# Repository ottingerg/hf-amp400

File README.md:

# hf-amp400

HF-Amp400 is controllerboard designed to controll the gate biasing and output power of 2 double HF-AMP FETs. 

It therefore provides 4 channels of gate biasing

4 channels of HF-Power mesaurement 

2 resetable fuses up to 10A and one auxilary resetable fuse controll for even higher currents.

This project was done as collaberation between

EMV-Consulting (http://www.emvconsulting.at)

Otelo eGen (http://www.oteloegen.at)

and

Karl Zeilhofer (http://www.zeilhofer.co.at)

it is Open Source Hardware licensed under CC-BY-SA 3.0 and is based on EtherDue which itself is based on Arduino Due

# EtherDue

The EtherDue is an 100% Arduino Due compatible board with onboard Ethernet.

For full details about the EtherDue, including a getting started guide, please visit the [Freetronics EtherDue product page](http://www.freetronics.com/products/etherdue-arduino-due-compatible-with-onboard-ethernet).

Design files were produced with [Kicad](http://kicad.org). A [PDF of the schematic is available](https://github.com/freetronics/EtherDue/raw/master/EtherDue.pdf).

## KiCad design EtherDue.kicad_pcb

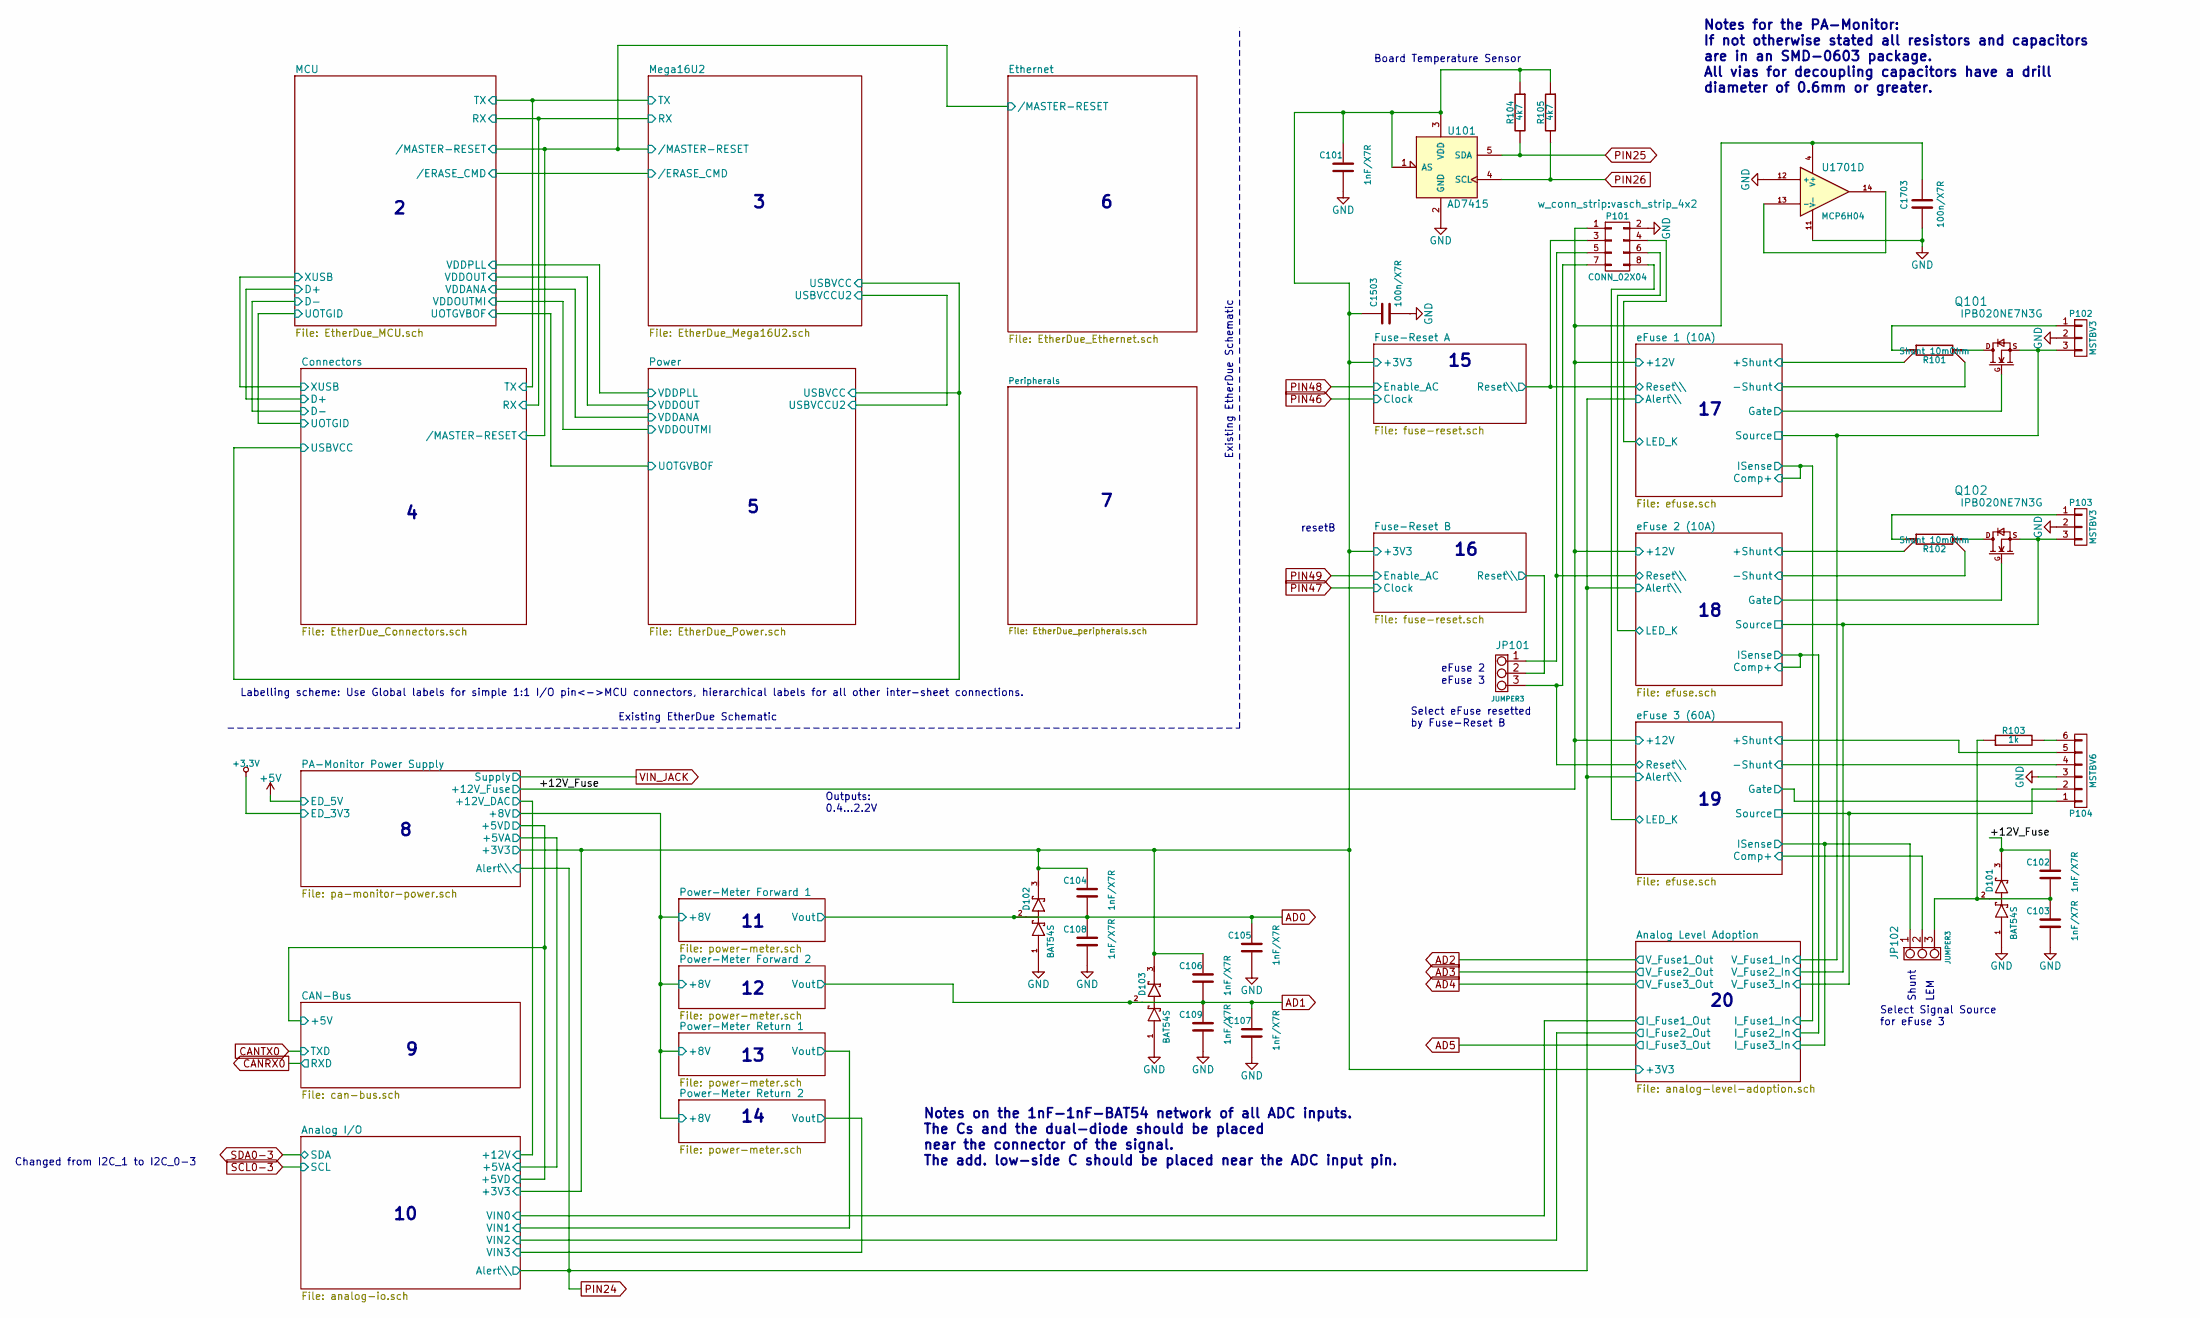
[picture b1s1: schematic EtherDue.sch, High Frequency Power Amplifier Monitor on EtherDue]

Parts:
C101, C102, C103, C104, C105, C106, C107, C108, C109: 1nF/X7R; C_0603
C1503, C1703: 100n/X7R; C_0603
D101, D102, D103: BAT54S; sot23
JP101, JP102: JUMPER3; Pin_Header_Straight_1x03
P101: CONN_02X04; vasch_strip_4x2
P102, P103: MSTBV3
P104: MSTBV6
Q101, Q102: IPB020NE7N3G; d2-pak
R101, R102: Shunt 10mOhm; WSL4026
R103: 1k; R_0603
R104, R105: 4k7; R_0603
U101: AD7415; SOT23-5
U1701: MCP6H04; SOIC-14_3.9x8.7mm_Pitch1.27mm

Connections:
/Analog I/O/+3V3: C101.1, C104.1, C106.1, C1503.1, D102.3 (cathode), D103.3 (cathode), R104.1, R105.1, U101.1 (AS), U101.3 (VDD); also elsewhere on the board
/Fuse-Reset B/Reset\: JP101.2; also elsewhere on the board
/eFuse 1 (10A)/+Shunt: R101.SA; also elsewhere on the board
/eFuse 1 (10A)/-Shunt: R101.SB; also elsewhere on the board
/eFuse 1 (10A)/Gate: Q101.G; also elsewhere on the board
/eFuse 1 (10A)/LED_K: P101.4; also elsewhere on the board
/eFuse 1 (10A)/Source: P102.3, Q101.S; also elsewhere on the board
/eFuse 2 (10A)/+Shunt: R102.SA; also elsewhere on the board
/eFuse 2 (10A)/-Shunt: R102.SB; also elsewhere on the board
/eFuse 2 (10A)/Gate: Q102.G; also elsewhere on the board
/eFuse 2 (10A)/LED_K: P101.6; also elsewhere on the board
/eFuse 2 (10A)/Reset\: JP101.1, P101.5; also elsewhere on the board
/eFuse 2 (10A)/Source: P103.3, Q102.S; also elsewhere on the board
/eFuse 3 (60A)/+Shunt: P104.5; also elsewhere on the board
/eFuse 3 (60A)/-Shunt: P104.4; also elsewhere on the board
/eFuse 3 (60A)/Comp+: JP102.2; also elsewhere on the board
/eFuse 3 (60A)/Gate: P104.1; also elsewhere on the board
/eFuse 3 (60A)/ISense: JP102.1; also elsewhere on the board
/eFuse 3 (60A)/LED_K: P101.8; also elsewhere on the board
/eFuse 3 (60A)/Reset\: JP101.3, P101.7; also elsewhere on the board
/eFuse 3 (60A)/Source: P104.2; also elsewhere on the board
AD0: C104.2, C105.1, C108.1, D102.2 (AK); also elsewhere on the board
AD1: C106.2, C107.1, C109.1, D103.2 (AK); also elsewhere on the board
unnamed: C102.2, C103.1, D101.2 (AK), JP102.3, R103.1
unnamed: P102.1, R101.A
unnamed: P103.1, R102.A
unnamed: P104.6, R103.2
unnamed: Q101.D, R101.B
unnamed: Q102.D, R102.B
unnamed: U1701.13 (-), U1701.14
PIN25: R104.2, U101.5 (SDA); also elsewhere on the board
PIN26: R105.2, U101.4 (SCL); also elsewhere on the board

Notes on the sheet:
Labelling scheme: Use Global labels for simple 1:1 I/O pin<->MCU connectors, hierarchical labels for all other inter-sheet connections.
Existing EtherDue Schematic
Outputs: 0.4...2.2V
resetB
Board Temperature Sensor
Notes for the PA-Monitor: If not otherwise stated all resistors and capacitors are in an SMD-0603 package. All vias for decoupling capacitors have a drill diameter of 0.6mm or greater.
Notes on the 1nF-1nF-BAT54 network of all ADC inputs. The Cs and the dual-diode should be placed near the connector of the signal. The add. low-side C should be placed near the ADC input pin.
Shunt
LEM
Select Signal Source for eFuse 3
Select eFuse resetted by Fuse-Reset B
eFuse 2
eFuse 3
Changed from I2C_1 to I2C_0-3

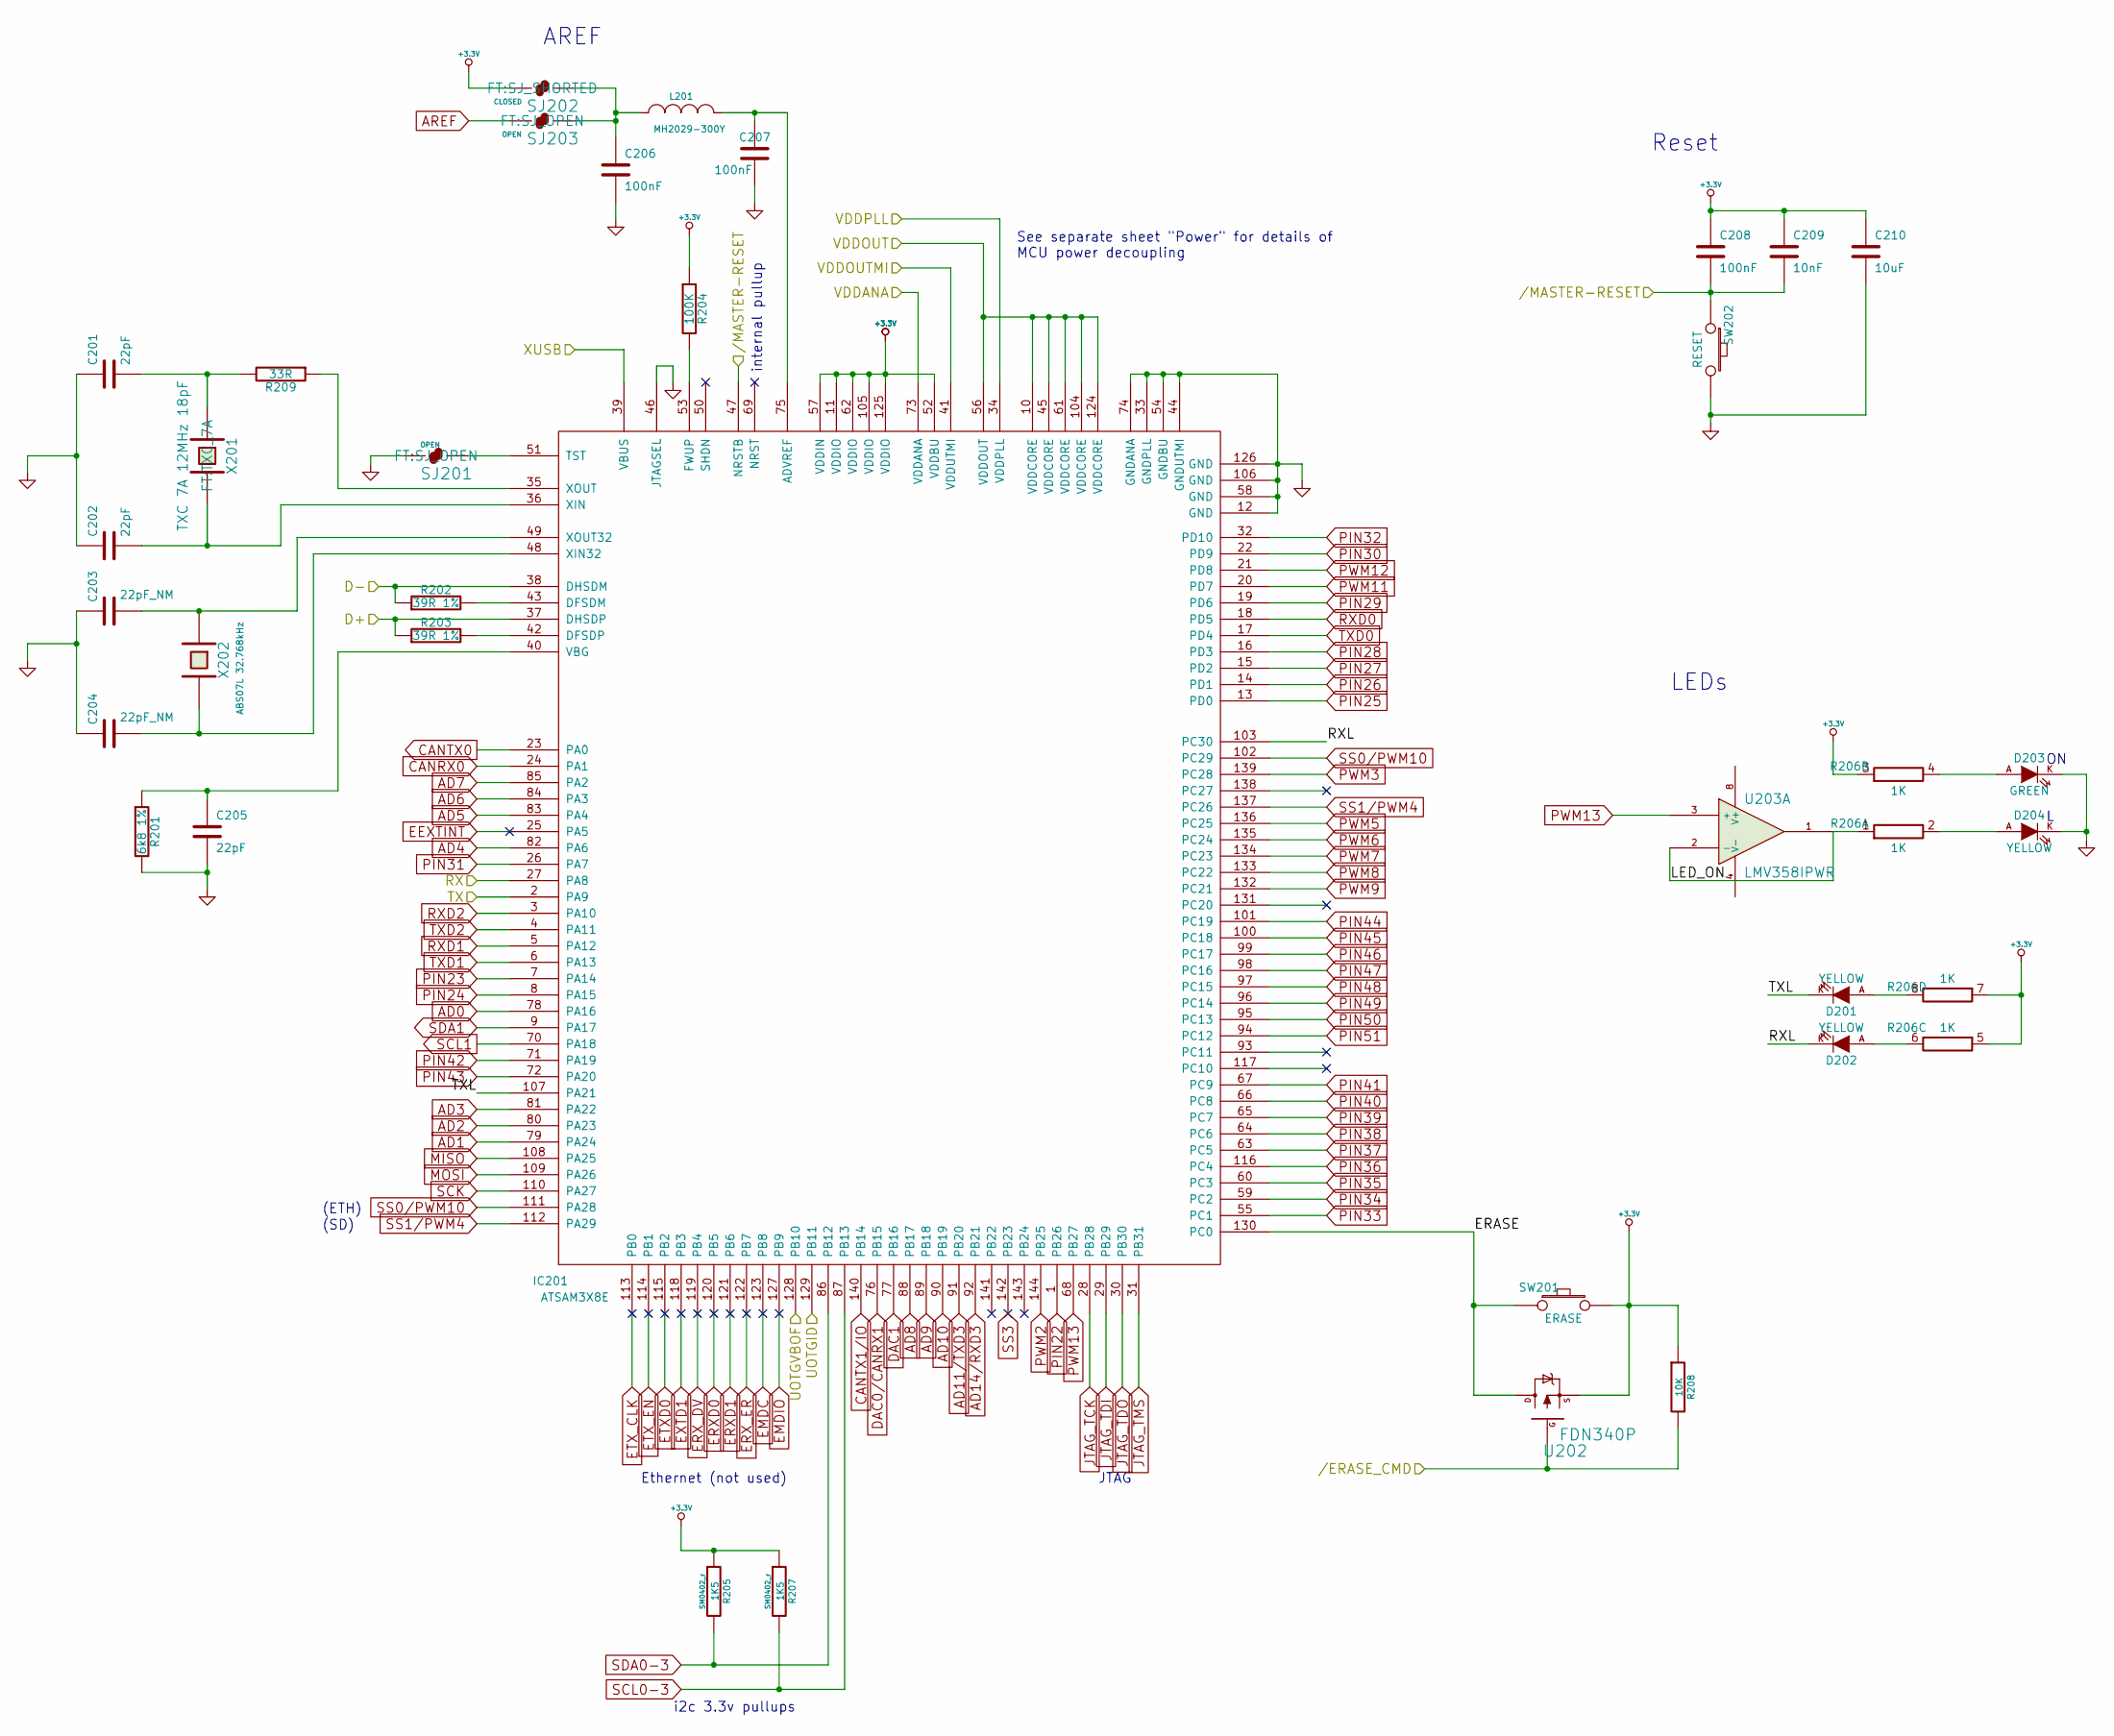
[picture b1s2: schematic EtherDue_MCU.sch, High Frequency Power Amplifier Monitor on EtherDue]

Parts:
C201, C202, C205: 22pF; SM0402
C203, C204: 22pF_NM; SM0402
C206, C207, C208: 100nF; SM0402
C209: 10nF; C0402
C210: 10uF; SM0603_Capa
D201, D202, D204: YELLOW; LED-0603
D203: GREEN; LED-0603
IC201: ATSAM3X8E; TQFP144
L201: MH2029-300Y; MH2029
R201: 6k8 1%; SM0402_r
R202, R203: 39R 1%; SM0402_r
R204: 100K; SM0402_r
R205, R207: 1K5; SM0402_r
R206: 1K; RES_CAY16
R208: 10K; SMD-0402_r
R209: 33R; R_0402
SJ201, SJ203: OPEN; SJ_OPEN
SJ202: CLOSED; SJ_SHORTED
SW201: ERASE; TACTILE_SWITCH_SMD_2PIN_TINY
SW202: RESET; TACTILE_SWITCH_SMD_2PIN_TINY
U202: FDN340P; SOT23_MOSFET
U203: LMV358IPWR; TSSOP8
X201: TXC 7A 12MHz 18pF; TXC_7A
X202: ABS07L 32.768kHz; ABS07L

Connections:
+3.3V: C208.1, C209.1, C210.1, IC201.11 (VDDIO), IC201.52 (VDDBU), IC201.57 (VDDIN), IC201.62 (VDDIO), IC201.105 (VDDIO), IC201.125 (VDDIO), R204.1, R205.1, R206.3 (7), R206.5 (7), R206.7, R207.1, R208.1, SJ202.1, SW201.2, U202.S; also elsewhere on the board
+5V: U203.8 (V+); also elsewhere on the board
/Connectors//MASTER-RESET: C208.2, C209.2, IC201.47 (NRSTB), SW202.1; also elsewhere on the board
/Connectors/D+: IC201.37 (DHSDP), R203.1; also elsewhere on the board
/Connectors/D-: IC201.38 (DHSDM), R202.1; also elsewhere on the board
/Connectors/RX: IC201.27 (PA8); also elsewhere on the board
/Connectors/TX: IC201.2 (PA9); also elsewhere on the board
/Connectors/UOTGID: IC201.129 (PB11); also elsewhere on the board
/Connectors/XUSB: IC201.39 (VBUS); also elsewhere on the board
/MCU//ERASE_CMD: R208.2, U202.G; also elsewhere on the board
/MCU/ERASE: IC201.130 (PC0), SW201.1, U202.D
/MCU/LED_ON: R206.1 (7), U203.1, U203.2 (-)
/MCU/RXL: D202.K, IC201.103 (PC30)
/MCU/TXL: D201.K, IC201.107 (PA21)
/MCU/UOTGVBOF: IC201.128 (PB10); also elsewhere on the board
/MCU/VDDANA: IC201.73 (VDDANA); also elsewhere on the board
/MCU/VDDOUT: IC201.10 (VDDCORE), IC201.45 (VDDCORE), IC201.56 (VDDOUT), IC201.61 (VDDCORE), IC201.104 (VDDCORE), IC201.124 (VDDCORE); also elsewhere on the board
/MCU/VDDOUTMI: IC201.41 (VDDUTMI); also elsewhere on the board
/MCU/VDDPLL: IC201.34 (VDDPLL); also elsewhere on the board
AD0: IC201.78 (PA16); also elsewhere on the board
AD1: IC201.79 (PA24); also elsewhere on the board
AD2: IC201.80 (PA23); also elsewhere on the board
AD3: IC201.81 (PA22); also elsewhere on the board
AD4: IC201.82 (PA6); also elsewhere on the board
AD5: IC201.83 (PA4); also elsewhere on the board
AD6: IC201.84 (PA3); also elsewhere on the board
AD7: IC201.85 (PA2); also elsewhere on the board
AD8: IC201.88 (PB17); also elsewhere on the board
AD9: IC201.89 (PB18); also elsewhere on the board
AD10: IC201.90 (PB19); also elsewhere on the board
AD11/TXD3: IC201.91 (PB20); also elsewhere on the board
AD14/RXD3: IC201.92 (PB21); also elsewhere on the board
AREF: SJ203.1; also elsewhere on the board
CANRX0: IC201.24 (PA1); also elsewhere on the board
CANTX0: IC201.23 (PA0); also elsewhere on the board
CANTX1/IO: IC201.140 (PB14); also elsewhere on the board
DAC0/CANRX1: IC201.76 (PB15); also elsewhere on the board
DAC1: IC201.77 (PB16); also elsewhere on the board
EEXTINT: IC201.25 (PA5)
EMDC: IC201.123 (PB8)
EMDIO: IC201.127 (PB9)
ERXD0: IC201.120 (PB5)
ERXD1: IC201.121 (PB6)
ERX_DV: IC201.119 (PB4)
ERX_ER: IC201.122 (PB7)
ETXD0: IC201.115 (PB2)
ETX_CLK: IC201.113 (PB0)
ETX_EN: IC201.114 (PB1)
EXTD1: IC201.118 (PB3)
JTAG_TCK: IC201.28 (PB28); also elsewhere on the board
JTAG_TDI: IC201.29 (PB29); also elsewhere on the board
JTAG_TDO: IC201.30 (PB30); also elsewhere on the board
JTAG_TMS: IC201.31 (PB31); also elsewhere on the board
MISO: IC201.108 (PA25); also elsewhere on the board
MOSI: IC201.109 (PA26); also elsewhere on the board
unnamed: C201.2, R209.2, X201.1
unnamed: C202.2, IC201.36 (XIN), X201.2
unnamed: C203.2, IC201.49 (XOUT32), X202.1
unnamed: C204.2, IC201.48 (XIN32), X202.2
unnamed: C205.1, IC201.40 (VBG), R201.1
unnamed: C206.1, L201.1, SJ202.2, SJ203.2
unnamed: C207.1, IC201.75 (ADVREF), L201.2
unnamed: D201.A, R206.8
unnamed: D202.A, R206.6 (8)
unnamed: D203.A, R206.4 (8)
unnamed: D204.A, R206.2 (8)
unnamed: IC201.35 (XOUT), R209.1
unnamed: IC201.42 (DFSDP), R203.2
unnamed: IC201.43 (DFSDM), R202.2
unnamed: IC201.51 (TST), SJ201.2
unnamed: IC201.53 (FWUP), R204.2
PIN22: IC201.1 (PB26); also elsewhere on the board
PIN23: IC201.7 (PA14); also elsewhere on the board
PIN24: IC201.8 (PA15); also elsewhere on the board
PIN25: IC201.13 (PD0); also elsewhere on the board
PIN26: IC201.14 (PD1); also elsewhere on the board
PIN27: IC201.15 (PD2); also elsewhere on the board
PIN28: IC201.16 (PD3); also elsewhere on the board
PIN29: IC201.19 (PD6); also elsewhere on the board
PIN30: IC201.22 (PD9); also elsewhere on the board
PIN31: IC201.26 (PA7); also elsewhere on the board
PIN32: IC201.32 (PD10); also elsewhere on the board
PIN33: IC201.55 (PC1); also elsewhere on the board
PIN34: IC201.59 (PC2); also elsewhere on the board
PIN35: IC201.60 (PC3); also elsewhere on the board
PIN36: IC201.116 (PC4); also elsewhere on the board
PIN37: IC201.63 (PC5); also elsewhere on the board
PIN38: IC201.64 (PC6); also elsewhere on the board
PIN39: IC201.65 (PC7); also elsewhere on the board
PIN40: IC201.66 (PC8); also elsewhere on the board
PIN41: IC201.67 (PC9); also elsewhere on the board
PIN42: IC201.71 (PA19); also elsewhere on the board
PIN43: IC201.72 (PA20); also elsewhere on the board
PIN44: IC201.101 (PC19); also elsewhere on the board
PIN45: IC201.100 (PC18); also elsewhere on the board
PIN46: IC201.99 (PC17); also elsewhere on the board
PIN47: IC201.98 (PC16); also elsewhere on the board
PIN48: IC201.97 (PC15); also elsewhere on the board
PIN49: IC201.96 (PC14); also elsewhere on the board
PIN50: IC201.95 (PC13); also elsewhere on the board
PIN51: IC201.94 (PC12); also elsewhere on the board
PWM2: IC201.144 (PB25); also elsewhere on the board
PWM3: IC201.139 (PC28); also elsewhere on the board
PWM5: IC201.136 (PC25); also elsewhere on the board
PWM6: IC201.135 (PC24); also elsewhere on the board
PWM7: IC201.134 (PC23); also elsewhere on the board
PWM8: IC201.133 (PC22); also elsewhere on the board
PWM9: IC201.132 (PC21); also elsewhere on the board
PWM11: IC201.20 (PD7); also elsewhere on the board
PWM12: IC201.21 (PD8); also elsewhere on the board
PWM13: IC201.68 (PB27), U203.3 (+); also elsewhere on the board
RXD0: IC201.18 (PD5); also elsewhere on the board
RXD1: IC201.5 (PA12); also elsewhere on the board
RXD2: IC201.3 (PA10); also elsewhere on the board
SCK: IC201.110 (PA27); also elsewhere on the board
SCL0-3: IC201.87 (PB13), R207.2; also elsewhere on the board
SCL1: IC201.70 (PA18); also elsewhere on the board
SDA0-3: IC201.86 (PB12), R205.2; also elsewhere on the board
SDA1: IC201.9 (PA17); also elsewhere on the board
SS0/PWM10: IC201.102 (PC29), IC201.111 (PA28); also elsewhere on the board
SS1/PWM4: IC201.112 (PA29), IC201.137 (PC26); also elsewhere on the board
SS3: IC201.142 (PB23)
TXD0: IC201.17 (PD4); also elsewhere on the board
TXD1: IC201.6 (PA13); also elsewhere on the board
TXD2: IC201.4 (PA11); also elsewhere on the board

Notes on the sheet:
i2c 3.3v pullups
Ethernet (not used)
JTAG
See separate sheet "Power" for details of MCU power decoupling
Reset
LEDs
AREF
(SD)
(ETH)
internal pullup

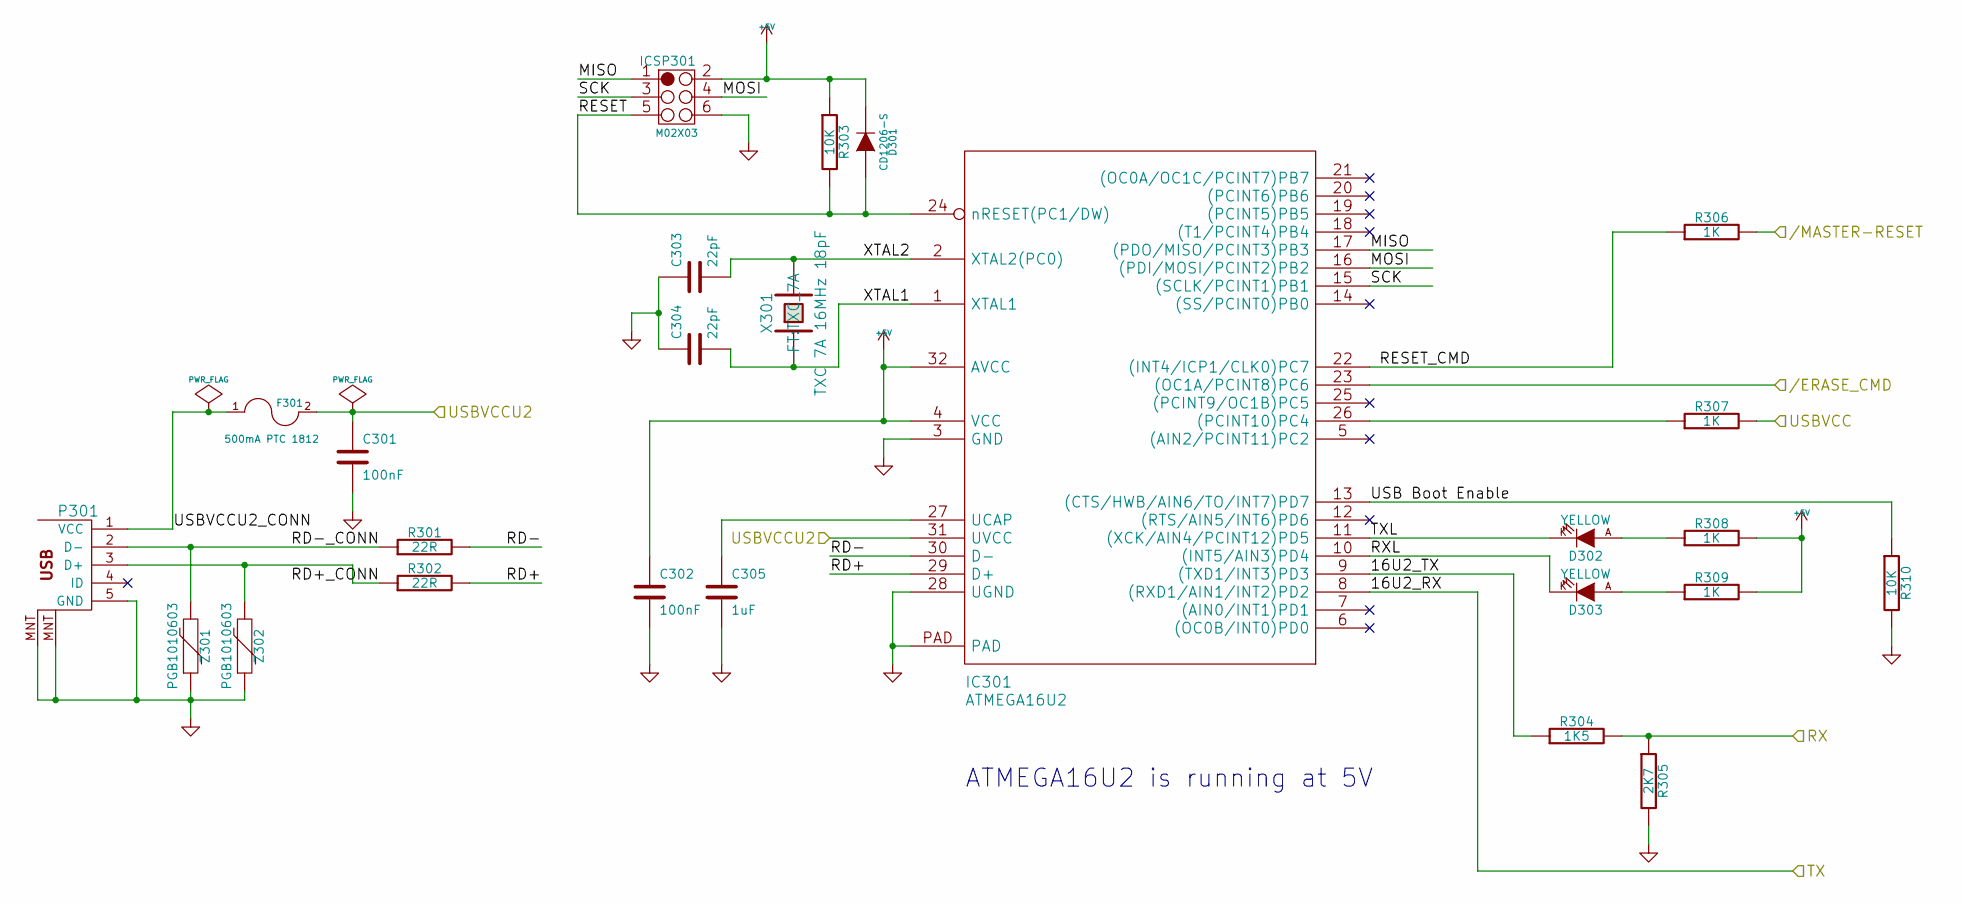
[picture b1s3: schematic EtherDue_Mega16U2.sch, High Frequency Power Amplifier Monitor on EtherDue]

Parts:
C301, C302: 100nF; SM0402
C303, C304: 22pF; SM0402
C305: 1uF; SM0402
D301: CD1206-S; 1206_DIODE
D302, D303: YELLOW; LED-0603
F301: 500mA PTC 1812; SM1812
IC301: ATMEGA16U2; QFN32
ICSP301: M02X03; Pin_Header_Straight_2x03
P301: USB_5PIN_SHELL; USB-MICRO_TH_4PEGS
R301, R302: 22R; SM0402_r
R303, R310: 10K; SM0402_r
R304: 1K5; SM0402_r
R305: 2K7; SM0402_r
R306, R307, R308, R309: 1K; SM0402_r
X301: TXC 7A 16MHz 18pF; TXC_7A
Z301, Z302: PGB1010603; 0603

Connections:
+5V: C302.1, D301.K, IC301.4 (VCC), IC301.32 (AVCC), ICSP301.2, R303.1, R308.2, R309.2; also elsewhere on the board
/Connectors//MASTER-RESET: R306.2; also elsewhere on the board
/Connectors/RX: R304.2, R305.1; also elsewhere on the board
/Connectors/TX: IC301.8 ((RXD1/AIN1/INT2)PD2); also elsewhere on the board
/Connectors/USBVCC: R307.2; also elsewhere on the board
/MCU//ERASE_CMD: IC301.23 ((OC1A/PCINT8)PC6); also elsewhere on the board
/Mega16U2/16U2_TX: IC301.9 ((TXD1/INT3)PD3), R304.1
/Mega16U2/MISO: IC301.17 ((PDO/MISO/PCINT3)PB3), ICSP301.1
/Mega16U2/MOSI: IC301.16 ((PDI/MOSI/PCINT2)PB2), ICSP301.4
/Mega16U2/RD+: IC301.29 (D+), R302.2
/Mega16U2/RD+_CONN: P301.3 (D+), R302.1, Z302.2
/Mega16U2/RD-: IC301.30 (D-), R301.2
/Mega16U2/RD-_CONN: P301.2 (D-), R301.1, Z301.2
/Mega16U2/RESET: D301.A, IC301.24 (nRESET(PC1/DW)), ICSP301.5, R303.2
/Mega16U2/RESET_CMD: IC301.22 ((INT4/ICP1/CLK0)PC7), R306.1
/Mega16U2/RXL: D303.K, IC301.10 ((INT5/AIN3)PD4)
/Mega16U2/SCK: IC301.15 ((SCLK/PCINT1)PB1), ICSP301.3
/Mega16U2/TXL: D302.K, IC301.11 ((XCK/AIN4/PCINT12)PD5)
/Mega16U2/USB Boot Enable: IC301.13 ((CTS/HWB/AIN6/TO/INT7)PD7), R310.1
/Mega16U2/USBVCCU2: C301.1, F301.2, IC301.31 (UVCC); also elsewhere on the board
/Mega16U2/USBVCCU2_CONN: F301.1, P301.1 (VCC)
/Mega16U2/XTAL1: C304.2, IC301.1 (XTAL1), X301.1
/Mega16U2/XTAL2: C303.2, IC301.2 (XTAL2(PC0)), X301.2
unnamed: C305.1, IC301.27 (UCAP)
unnamed: D302.A, R308.1
unnamed: D303.A, R309.1
unnamed: IC301.26 ((PCINT10)PC4), R307.1

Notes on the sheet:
ATMEGA16U2 is running at 5V

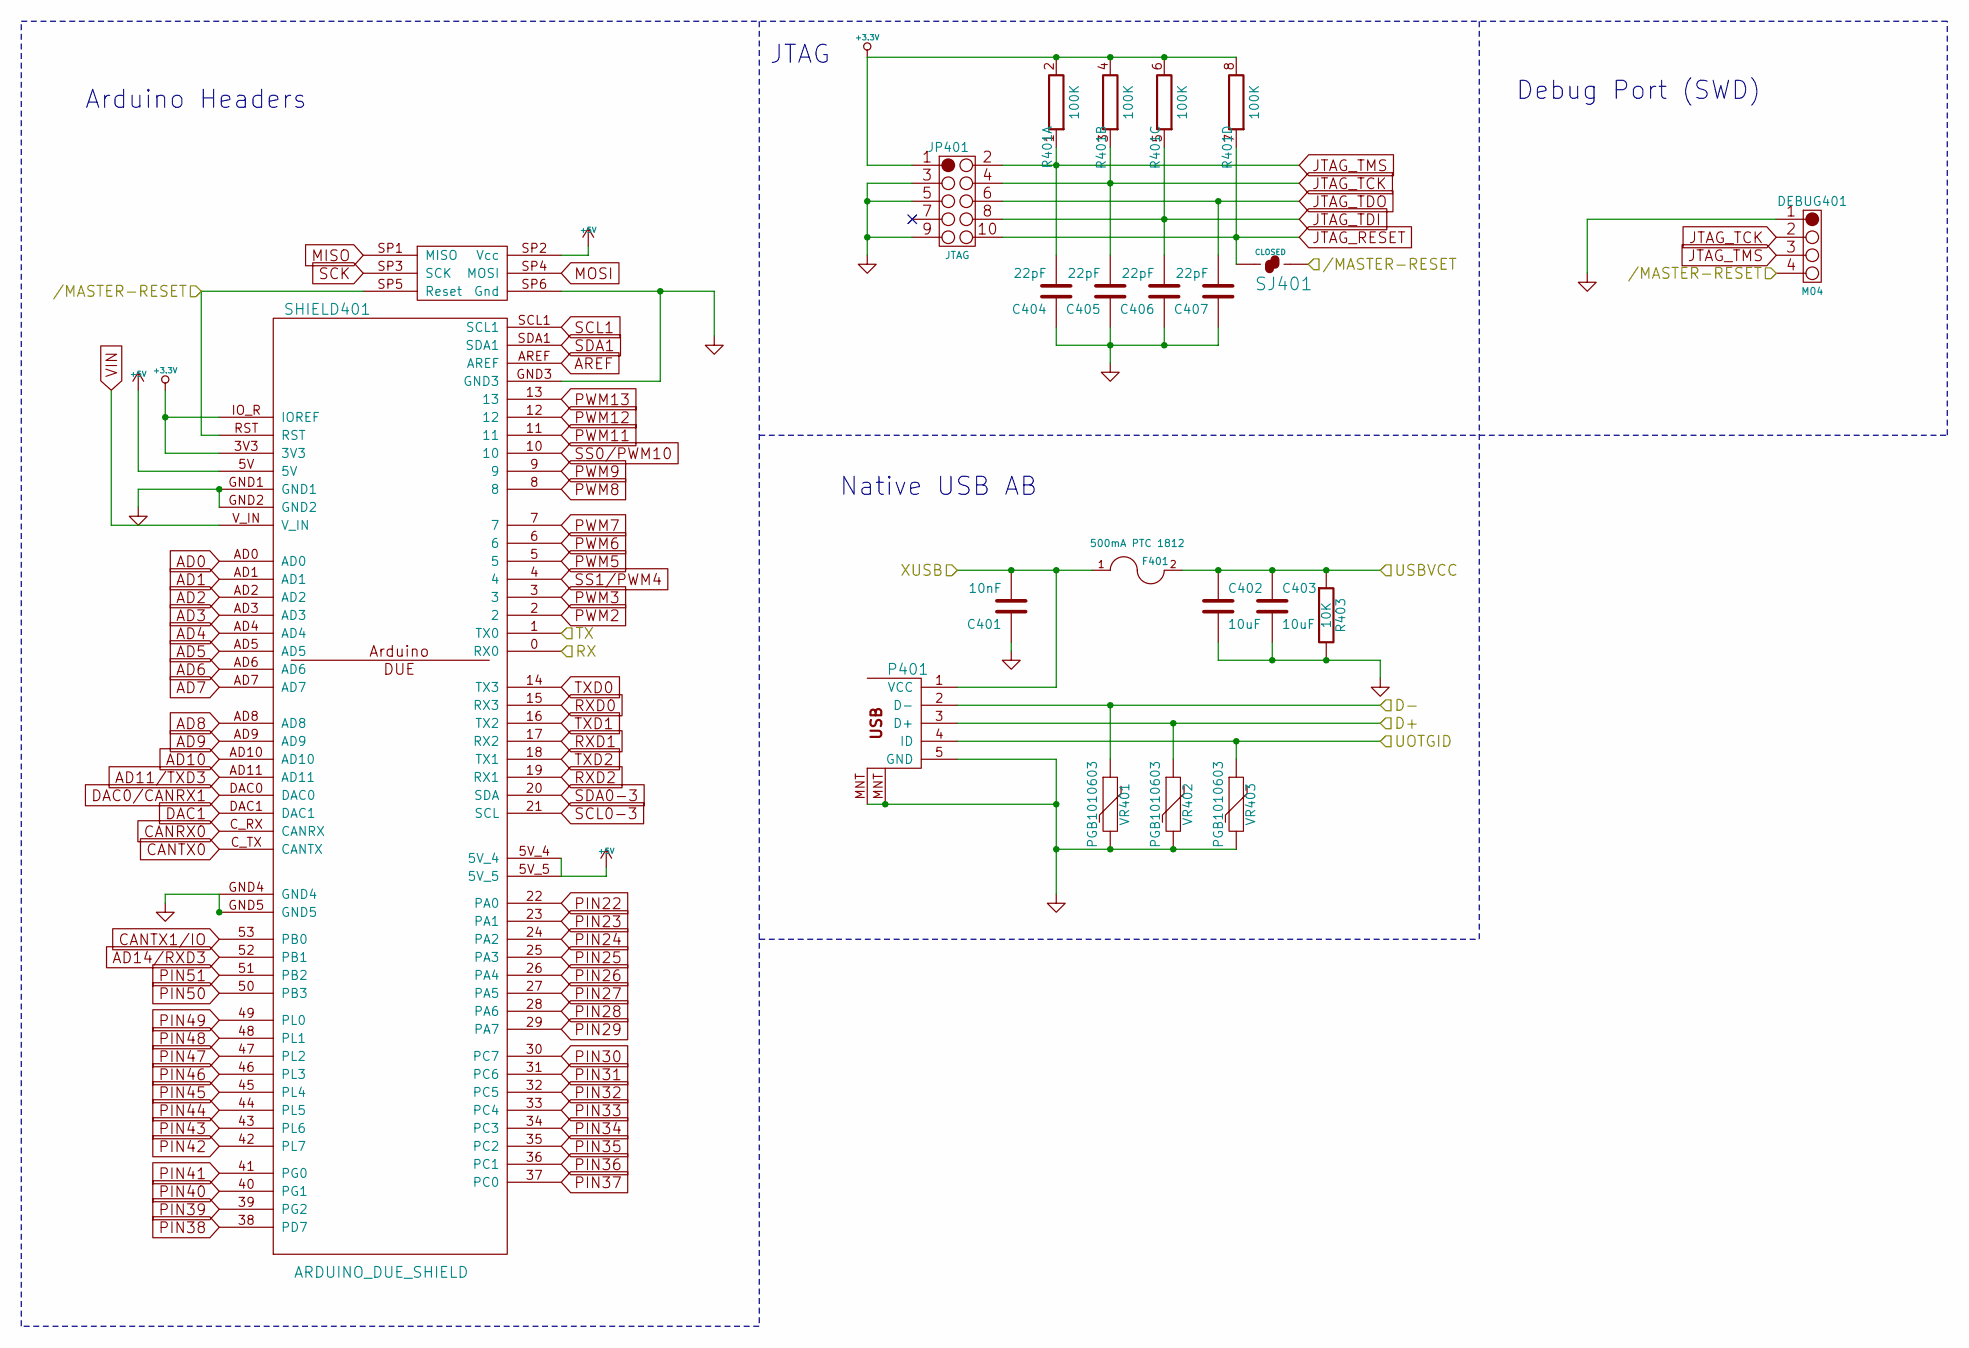
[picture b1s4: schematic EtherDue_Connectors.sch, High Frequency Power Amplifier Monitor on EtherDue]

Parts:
C401: 10nF; SM0402
C402, C403: 10uF; SM0603_Capa
C404, C405, C406, C407: 22pF; C0402
DEBUG401: M04; Pin_Header_Straight_1x04
F401: 500mA PTC 1812; SM1812
JP401: JTAG; 2X5_127MMPITCH
P401: USB_5PIN_SHELL; USB-MICRO_TH_4PEGS
R401: 100K; RES_CAY16
R403: 10K; SM0402_r
SHIELD401: ARDUINO_DUE_SHIELD
SJ401: CLOSED; SJ_SHORTED
VR401, VR402, VR403: PGB1010603; 0603

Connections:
+3.3V: JP401.1, R401.2 (8), R401.4 (8), R401.6 (8), R401.8, SHIELD401.3V3, SHIELD401.IO_R (IOREF); also elsewhere on the board
+5V: SHIELD401.5V, SHIELD401.5V_4, SHIELD401.5V_5, SHIELD401.SP2 (Vcc); also elsewhere on the board
/Connectors//MASTER-RESET: DEBUG401.4, SHIELD401.RST, SHIELD401.SP5 (Reset), SJ401.2; also elsewhere on the board
/Connectors/D+: P401.3 (D+), VR402.1; also elsewhere on the board
/Connectors/D-: P401.2 (D-), VR401.1; also elsewhere on the board
/Connectors/RX: SHIELD401.0 (RX0); also elsewhere on the board
/Connectors/TX: SHIELD401.1 (TX0); also elsewhere on the board
/Connectors/UOTGID: P401.4 (ID), VR403.1; also elsewhere on the board
/Connectors/USBVCC: C402.1, C403.1, F401.2, R403.1; also elsewhere on the board
/Connectors/XUSB: C401.2, F401.1, P401.1 (VCC); also elsewhere on the board
AD0: SHIELD401.AD0; also elsewhere on the board
AD1: SHIELD401.AD1; also elsewhere on the board
AD2: SHIELD401.AD2; also elsewhere on the board
AD3: SHIELD401.AD3; also elsewhere on the board
AD4: SHIELD401.AD4; also elsewhere on the board
AD5: SHIELD401.AD5; also elsewhere on the board
AD6: SHIELD401.AD6; also elsewhere on the board
AD7: SHIELD401.AD7; also elsewhere on the board
AD8: SHIELD401.AD8; also elsewhere on the board
AD9: SHIELD401.AD9; also elsewhere on the board
AD10: SHIELD401.AD10; also elsewhere on the board
AD11/TXD3: SHIELD401.AD11; also elsewhere on the board
AD14/RXD3: SHIELD401.52 (PB1); also elsewhere on the board
AREF: SHIELD401.AREF; also elsewhere on the board
CANRX0: SHIELD401.C_RX (CANRX); also elsewhere on the board
CANTX0: SHIELD401.C_TX (CANTX); also elsewhere on the board
CANTX1/IO: SHIELD401.53 (PB0); also elsewhere on the board
DAC0/CANRX1: SHIELD401.DAC0; also elsewhere on the board
DAC1: SHIELD401.DAC1; also elsewhere on the board
JTAG_RESET: JP401.10, R401.7, SJ401.1
JTAG_TCK: C405.2, DEBUG401.2, JP401.4, R401.3 (7); also elsewhere on the board
JTAG_TDI: C406.2, JP401.8, R401.5 (7); also elsewhere on the board
JTAG_TDO: C407.2, JP401.6; also elsewhere on the board
JTAG_TMS: C404.2, DEBUG401.3, JP401.2, R401.1 (7); also elsewhere on the board
MISO: SHIELD401.SP1 (MISO); also elsewhere on the board
MOSI: SHIELD401.SP4 (MOSI); also elsewhere on the board
PIN22: SHIELD401.22 (PA0); also elsewhere on the board
PIN23: SHIELD401.23 (PA1); also elsewhere on the board
PIN24: SHIELD401.24 (PA2); also elsewhere on the board
PIN25: SHIELD401.25 (PA3); also elsewhere on the board
PIN26: SHIELD401.26 (PA4); also elsewhere on the board
PIN27: SHIELD401.27 (PA5); also elsewhere on the board
PIN28: SHIELD401.28 (PA6); also elsewhere on the board
PIN29: SHIELD401.29 (PA7); also elsewhere on the board
PIN30: SHIELD401.30 (PC7); also elsewhere on the board
PIN31: SHIELD401.31 (PC6); also elsewhere on the board
PIN32: SHIELD401.32 (PC5); also elsewhere on the board
PIN33: SHIELD401.33 (PC4); also elsewhere on the board
PIN34: SHIELD401.34 (PC3); also elsewhere on the board
PIN35: SHIELD401.35 (PC2); also elsewhere on the board
PIN36: SHIELD401.36 (PC1); also elsewhere on the board
PIN37: SHIELD401.37 (PC0); also elsewhere on the board
PIN38: SHIELD401.38 (PD7); also elsewhere on the board
PIN39: SHIELD401.39 (PG2); also elsewhere on the board
PIN40: SHIELD401.40 (PG1); also elsewhere on the board
PIN41: SHIELD401.41 (PG0); also elsewhere on the board
PIN42: SHIELD401.42 (PL7); also elsewhere on the board
PIN43: SHIELD401.43 (PL6); also elsewhere on the board
PIN44: SHIELD401.44 (PL5); also elsewhere on the board
PIN45: SHIELD401.45 (PL4); also elsewhere on the board
PIN46: SHIELD401.46 (PL3); also elsewhere on the board
PIN47: SHIELD401.47 (PL2); also elsewhere on the board
PIN48: SHIELD401.48 (PL1); also elsewhere on the board
PIN49: SHIELD401.49 (PL0); also elsewhere on the board
PIN50: SHIELD401.50 (PB3); also elsewhere on the board
PIN51: SHIELD401.51 (PB2); also elsewhere on the board
PWM2: SHIELD401.2; also elsewhere on the board
PWM3: SHIELD401.3; also elsewhere on the board
PWM5: SHIELD401.5; also elsewhere on the board
PWM6: SHIELD401.6; also elsewhere on the board
PWM7: SHIELD401.7; also elsewhere on the board
PWM8: SHIELD401.8; also elsewhere on the board
PWM9: SHIELD401.9; also elsewhere on the board
PWM11: SHIELD401.11; also elsewhere on the board
PWM12: SHIELD401.12; also elsewhere on the board
PWM13: SHIELD401.13; also elsewhere on the board
RXD0: SHIELD401.15 (RX3); also elsewhere on the board
RXD1: SHIELD401.17 (RX2); also elsewhere on the board
RXD2: SHIELD401.19 (RX1); also elsewhere on the board
SCK: SHIELD401.SP3 (SCK); also elsewhere on the board
SCL0-3: SHIELD401.21 (SCL); also elsewhere on the board
SCL1: SHIELD401.SCL1; also elsewhere on the board
SDA0-3: SHIELD401.20 (SDA); also elsewhere on the board
SDA1: SHIELD401.SDA1; also elsewhere on the board
SS0/PWM10: SHIELD401.10; also elsewhere on the board
SS1/PWM4: SHIELD401.4; also elsewhere on the board
TXD0: SHIELD401.14 (TX3); also elsewhere on the board
TXD1: SHIELD401.16 (TX2); also elsewhere on the board
TXD2: SHIELD401.18 (TX1); also elsewhere on the board
VIN: SHIELD401.V_IN; also elsewhere on the board

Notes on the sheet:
Debug Port (SWD)
Native USB AB
JTAG
Arduino Headers

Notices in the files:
EtherDue.kicad_pcb:
Under Creative Commons Attribution ShareAlike License
Licensed by Freetronics Pty Ltd
EtherDue.sch:
Derived from EtherDue - (C) 2014 Freetronics Pty Ltd
Licensed under Creative Commons Share-Alike
